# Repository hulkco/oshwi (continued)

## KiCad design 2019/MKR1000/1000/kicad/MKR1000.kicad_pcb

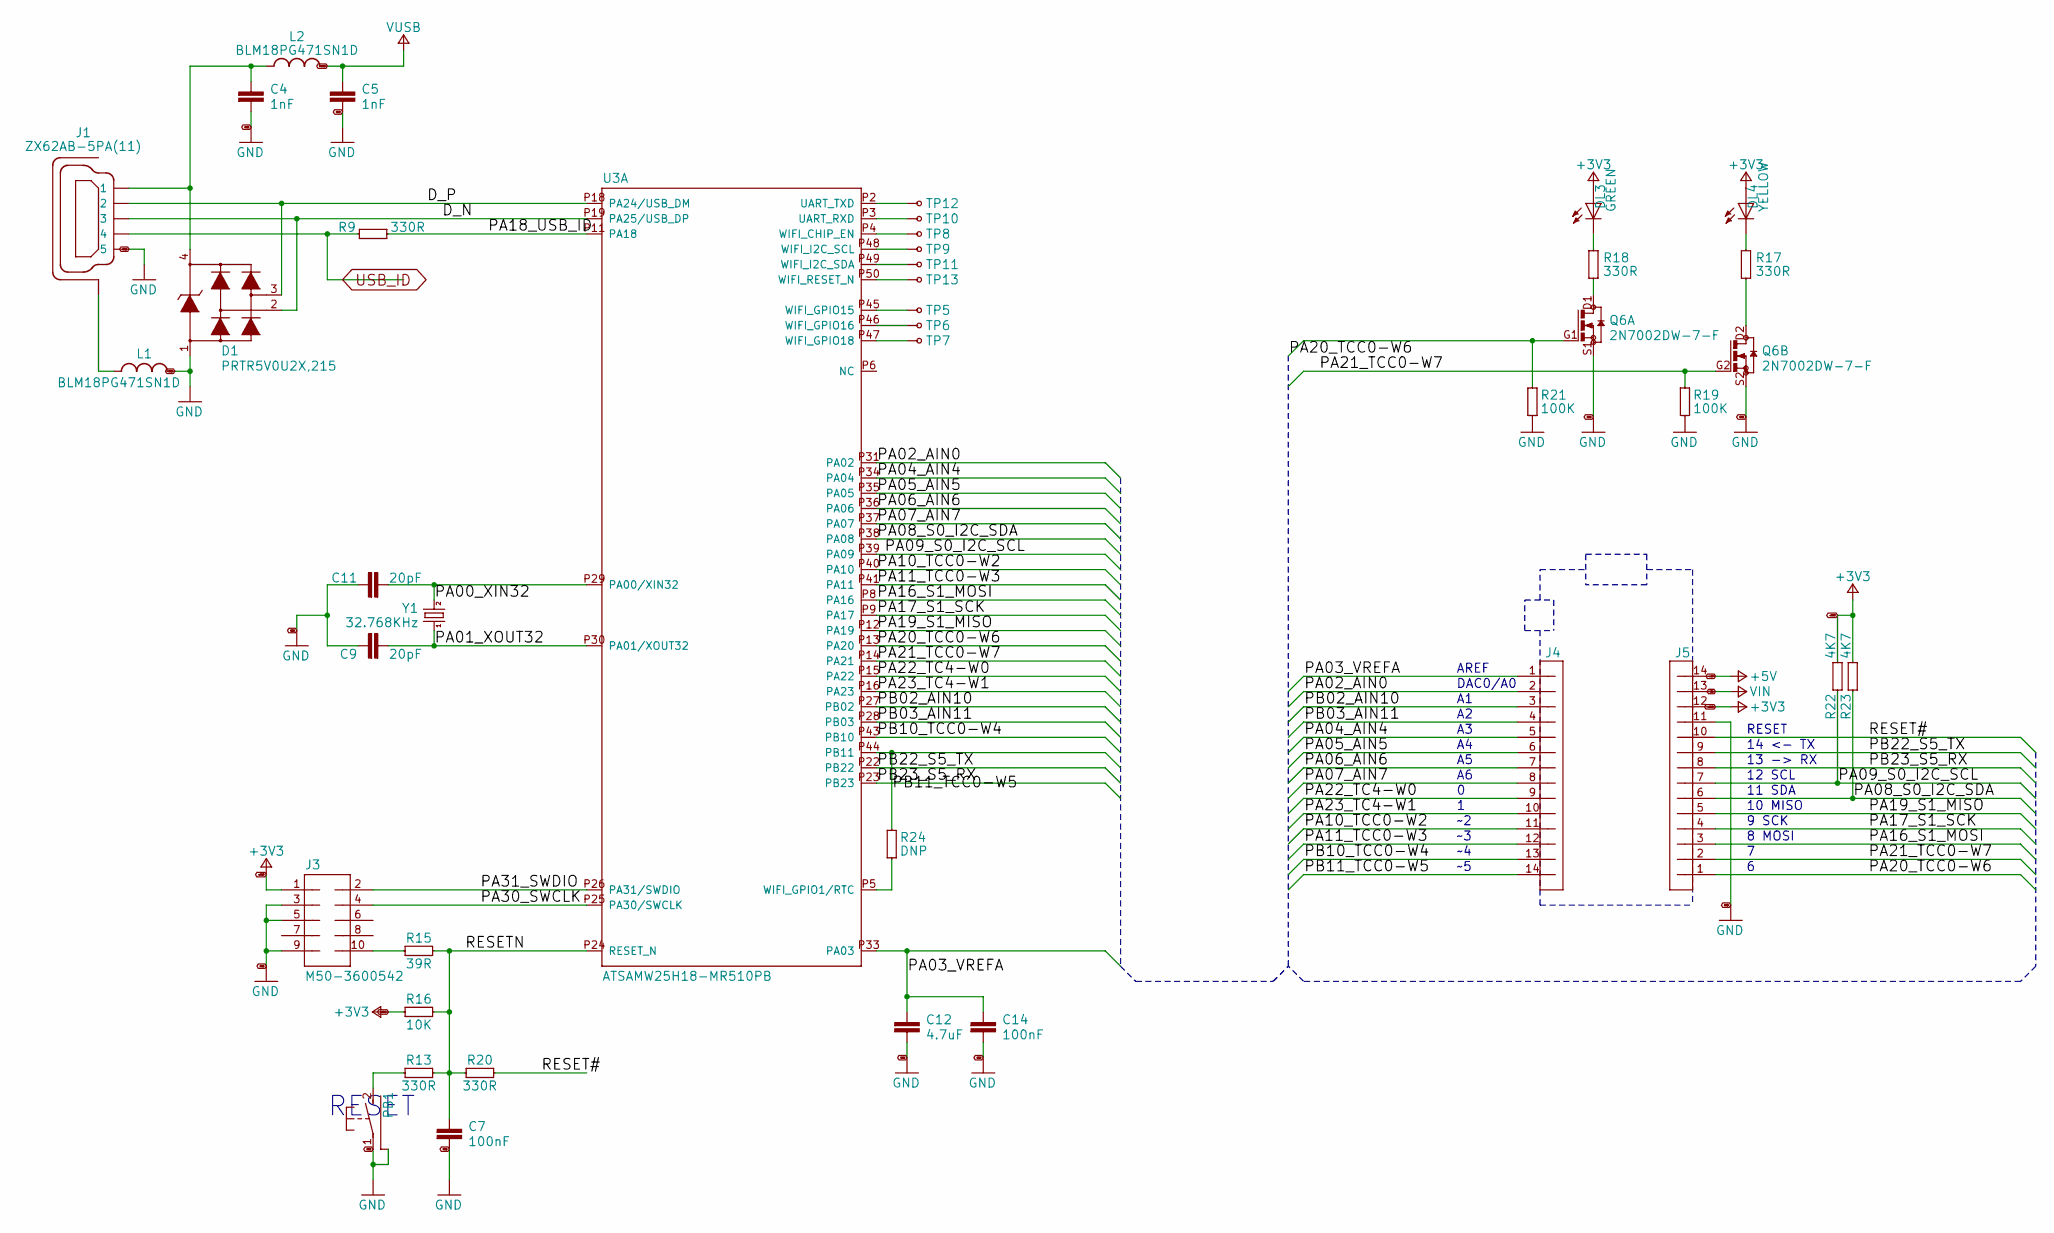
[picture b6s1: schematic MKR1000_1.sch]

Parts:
C4, C5: 1nF; 0402-1005X55N
C7, C14: 100nF; 0402-1005X55N
C9, C11: 20pF; 0402-1005X55N
C12: 4.7uF; 0402-1005X55N
D1: PRTR5V0U2X,215; SOT190P230X110-4N
DL3: GREEN; LEDC1608X80N-AK
DL4: YELLOW; LEDC1608X80N-AK
J1: ZX62AB-5PA(11); USBMICRO-ZX62-AB-5PA
J3: M50-3600542; FCI-MINITEK127HDR-10
J4, J5: DNP; STRIP-14-MODULI-A11
L1, L2: BLM18PG471SN1D; 0603-1608X90N
PB1: PTS820; PULS-45X29-PST820
Q6: 2N7002DW-7-F; SOT65P210X110-6AN-DM
R9, R13, R17, R18, R20: 330R; 0402-1005X55N
R15: 39R; 0402-1005X55N
R16: 10K; 0402-1005X55N
R19, R21: 100K; 0402-1005X55N
R22, R23: 4K7; 0402-1005X55N
R24: DNP; 0402-1005X55N
TP5, TP6, TP7, TP8, TP9, TP10, TP11, TP12, TP13: TESTPAD; PAD-SMD
U3: ATSAMW25H18-MR510PB; SAMW25
Y1: 32.768KHz; QUARZO-ABS07

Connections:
+3V3: DL3.A, DL4.A, J3.1, J5.12, R16.1, R22.2, R23.2; also elsewhere on the board
+5V: J5.14; also elsewhere on the board
/MKR1000_1/D_N: D1.2, J1.3, U3.P19 (PA25/USB_DP)
/MKR1000_1/D_P: D1.3, J1.2, U3.P18 (PA24/USB_DM)
/MKR1000_1/PA00_XIN32: C11.2, U3.P29 (PA00/XIN32), Y1.2
/MKR1000_1/PA01_XOUT32: C9.2, U3.P30 (PA01/XOUT32), Y1.1
/MKR1000_1/PA02_AIN0: J4.2, U3.P31 (PA02)
/MKR1000_1/PA03_VREFA: C12.1, C14.1, J4.1, U3.P33 (PA03)
/MKR1000_1/PA04_AIN4: J4.5, U3.P34 (PA04)
/MKR1000_1/PA05_AIN5: J4.6, U3.P35 (PA05)
/MKR1000_1/PA06_AIN6: J4.7, U3.P36 (PA06)
/MKR1000_1/PA07_AIN7: J4.8, U3.P37 (PA07)
/MKR1000_1/PA08_S0_I2C_SDA: J5.6, R23.1, U3.P38 (PA08)
/MKR1000_1/PA09_S0_I2C_SCL: J5.7, R22.1, U3.P39 (PA09)
/MKR1000_1/PA10_TCC0-W2: J4.11, U3.P40 (PA10)
/MKR1000_1/PA11_TCC0-W3: J4.12, U3.P41 (PA11)
/MKR1000_1/PA16_S1_MOSI: J5.3, U3.P8 (PA16)
/MKR1000_1/PA17_S1_SCK: J5.4, U3.P9 (PA17)
/MKR1000_1/PA18_USB_ID: R9.2, U3.P11 (PA18)
/MKR1000_1/PA19_S1_MISO: J5.5, U3.P12 (PA19)
/MKR1000_1/PA20_TCC0-W6: J5.1, Q6.G1 (G), R21.2, U3.P13 (PA20)
/MKR1000_1/PA21_TCC0-W7: J5.2, Q6.G2 (G), R19.2, U3.P14 (PA21)
/MKR1000_1/PA22_TC4-W0: J4.9, U3.P15 (PA22)
/MKR1000_1/PA23_TC4-W1: J4.10, U3.P16 (PA23)
/MKR1000_1/PA30_SWCLK: J3.4, U3.P25 (PA30/SWCLK)
/MKR1000_1/PA31_SWDIO: J3.2, U3.P26 (PA31/SWDIO)
/MKR1000_1/PB02_AIN10: J4.3, U3.P27 (PB02)
/MKR1000_1/PB03_AIN11: J4.4, U3.P28 (PB03)
/MKR1000_1/PB10_TCC0-W4: J4.13, U3.P43 (PB10)
/MKR1000_1/PB11_TCC0-W5: J4.14, R24.2, U3.P44 (PB11)
/MKR1000_1/PB22_S5_TX: J5.9, U3.P22 (PB22)
/MKR1000_1/PB23_S5_RX: J5.8, U3.P23 (PB23)
/MKR1000_1/RESET#: J5.10, R20.2
/MKR1000_1/RESETN: C7.1, R13.2, R15.2, R16.2, R20.1, U3.P24 (RESET_N)
GND: C4.2, C5.2, C7.2, C9.1, C11.1, C12.2, C14.2, D1.1, J1.5, J3.3, J3.5, J3.9, J5.11, L1.2, PB1.1, PB1.3 (SH), PB1.4 (SH), PB1.5 (SH), PB1.6 (SH), Q6.S1 (S), Q6.S2 (S), R19.1, R21.1; also elsewhere on the board
unnamed: C4.1, D1.4, J1.1, L2.1
unnamed: DL3.C, R18.2
unnamed: DL4.C, R17.2
unnamed: J1.6 (SH), J1.7 (SH), J1.8 (SH), J1.9 (SH), J1.10 (SH), J1.11 (SH), L1.1
unnamed: J3.10, R15.1
unnamed: PB1.2 (S), R13.1
unnamed: Q6.D1 (D), R18.1
unnamed: Q6.D2 (D), R17.1
unnamed: R24.1, U3.P5 (WIFI_GPIO1/RTC)
unnamed: TP5.1, U3.P45 (WIFI_GPIO15)
unnamed: TP6.1, U3.P46 (WIFI_GPIO16)
unnamed: TP7.1, U3.P47 (WIFI_GPIO18)
unnamed: TP8.1, U3.P4 (WIFI_CHIP_EN)
unnamed: TP9.1, U3.P48 (WIFI_I2C_SCL)
unnamed: TP10.1, U3.P3 (UART_RXD)
unnamed: TP11.1, U3.P49 (WIFI_I2C_SDA)
unnamed: TP12.1, U3.P2 (UART_TXD)
unnamed: TP13.1, U3.P50 (WIFI_RESET_N)
USB_ID: J1.4, R9.1; also elsewhere on the board
VIN: J5.13; also elsewhere on the board
VUSB: C5.1, L2.2; also elsewhere on the board

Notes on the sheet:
14 <- TX
13 -> RX
12 SCL
RESET
11 SDA
8 MOSI
9 SCK
10 MISO
AREF
DAC0/A0
~~2
~~3
~~4
~~5

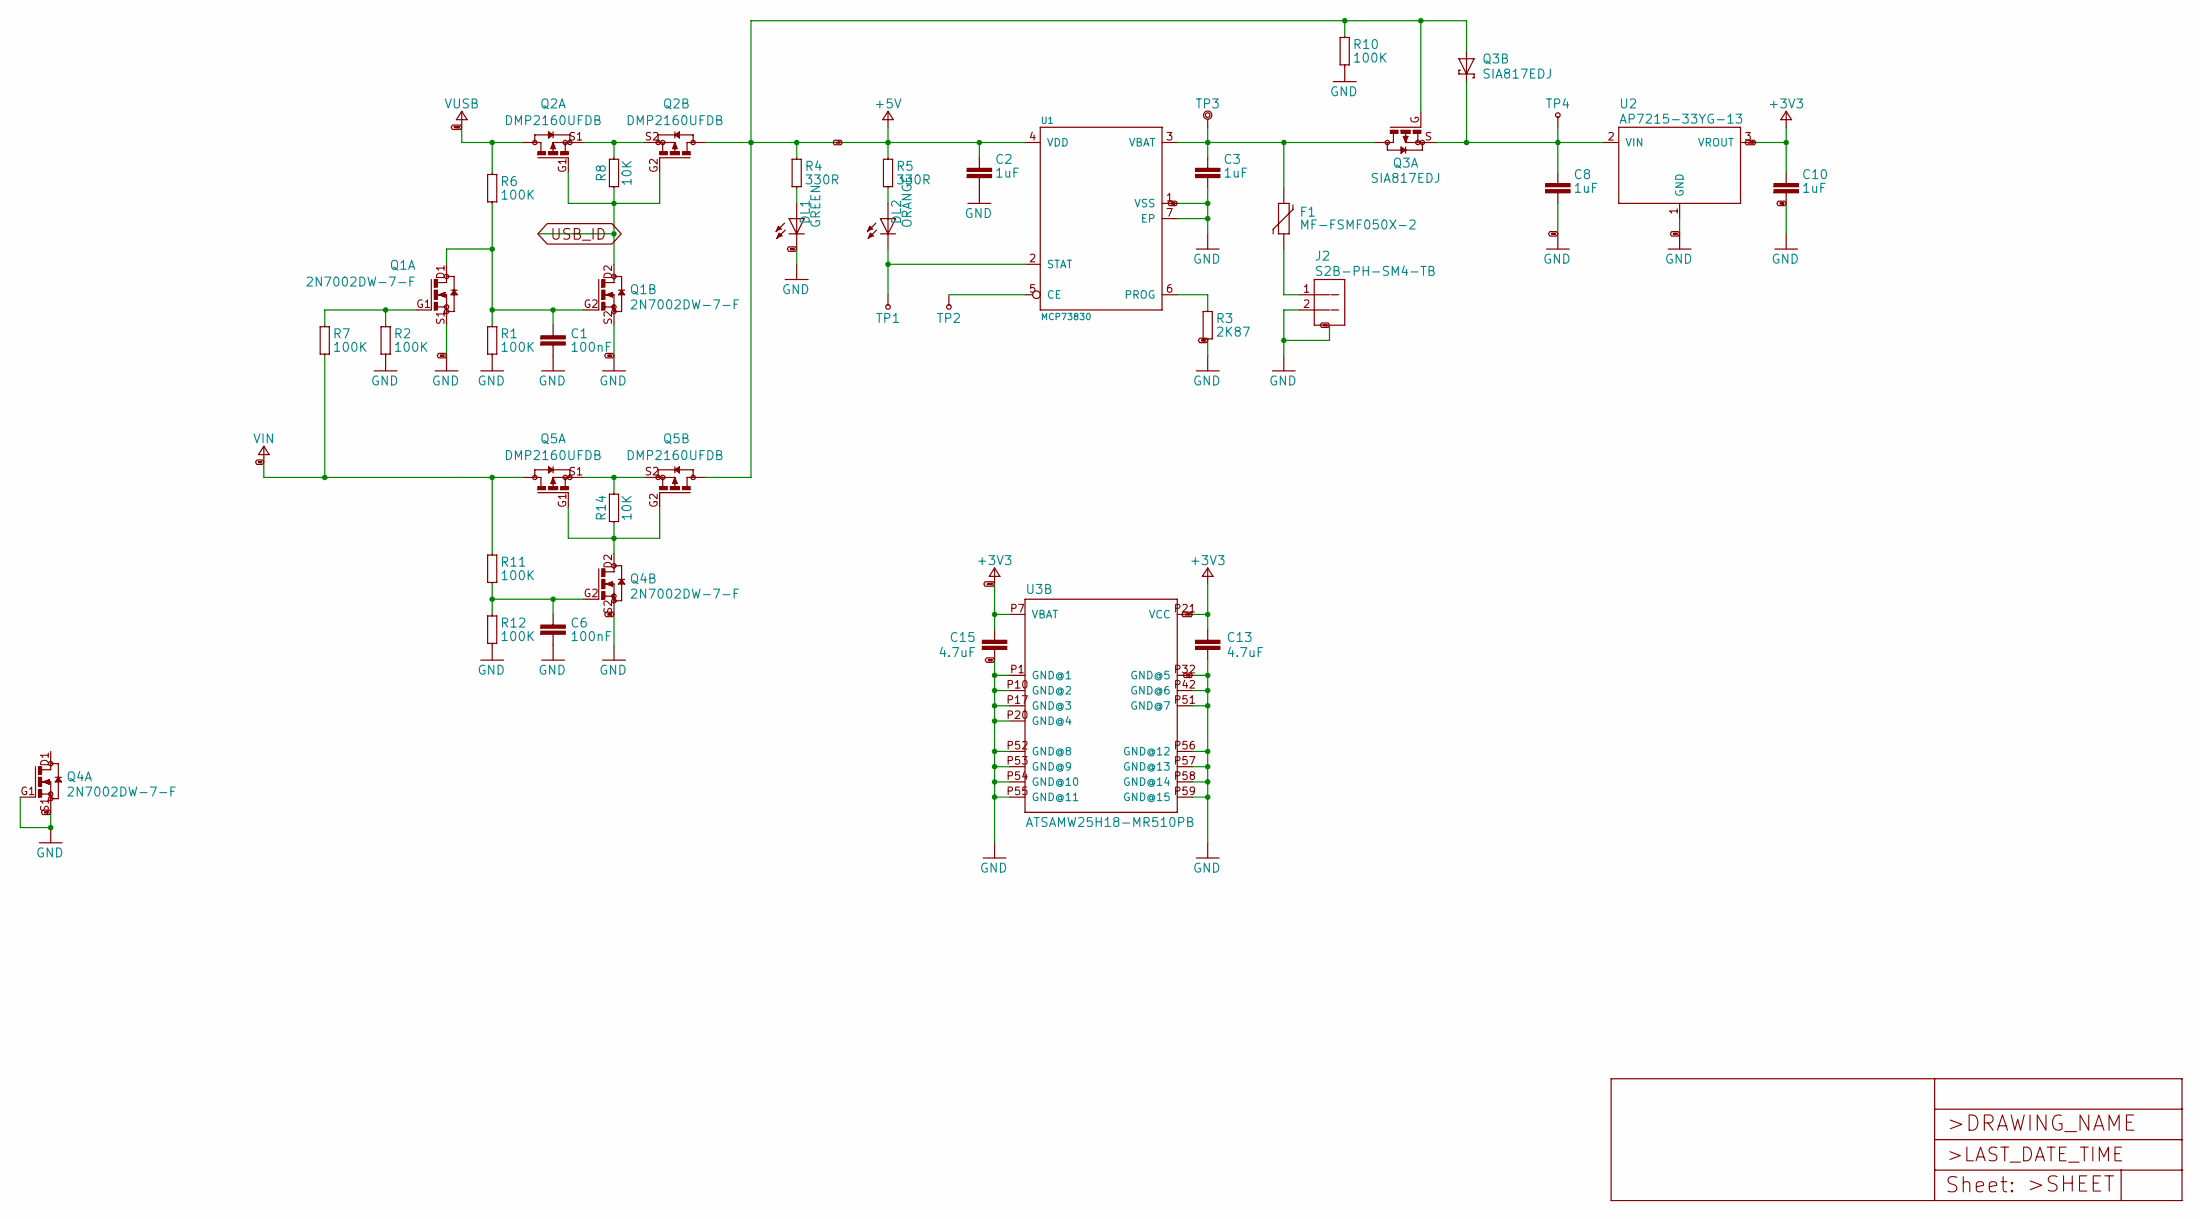
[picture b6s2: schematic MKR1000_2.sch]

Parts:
C1, C6: 100nF; 0402-1005X55N
C2, C3, C8, C10: 1uF; 0402-1005X55N; VOLTAGE 25V
C13, C15: 4.7uF; 0402-1005X55N
DL1: GREEN; LEDC1608X80N-AK
DL2: ORANGE; LEDC1608X80N-AK
F1: MF-FSMF050X-2; 0603-F1608X100N
FRAME2: Page 2; FRAME-NO-BAN-FRAMEONLY
J2: S2B-PH-SM4-TB; JST-S2B-PH-SM4-TB
Q1, Q4: 2N7002DW-7-F; SOT65P210X110-6AN-DM
Q2, Q5: DMP2160UFDB; SON65P200X200X60-8N-DM
Q3: SIA817EDJ; SON65P205X205X75-8N-MWSD
R1, R2, R6, R7, R10, R11, R12: 100K; 0402-1005X55N
R3: 2K87; 0805-R2013X50N
R4, R5: 330R; 0402-1005X55N
R8, R14: 10K; 0402-1005X55N
TP1, TP2, TP4: TESTPAD; PAD-SMD
TP3: TESTPOINT; TESTPOINT-60MLS-F0_9MM
U1: MCP73830; SON50P200X200X80-7N-EP160X60
U2: AP7215-33YG-13; SOT150P400X160-3N
U3: ATSAMW25H18-MR510PB; SAMW25

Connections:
+3V3: C10.1, C13.1, C15.1, U2.3 (VROUT), U3.P7 (VBAT), U3.P21 (VCC); also elsewhere on the board
+5V: C2.1, Q2.D2 (D), Q2.D2' (D), Q3.A, Q3.G, Q5.D2 (D), Q5.D2' (D), R4.2, R5.2, R10.2, U1.4 (VDD); also elsewhere on the board
GND: C1.2, C2.2, C3.2, C6.2, C8.2, C10.2, C13.2, C15.2, DL1.C, J2.2, J2.3 (SH), J2.4 (SH), Q1.S1 (S), Q1.S2 (S), Q4.G1 (G), Q4.S1 (S), Q4.S2 (S), R1.1, R2.1, R3.1, R10.1, R12.1, U1.1 (VSS), U1.7 (EP), U2.1 (GND), U3.P1 (GND@1), U3.P10 (GND@2), U3.P17 (GND@3), U3.P20 (GND@4), U3.P32 (GND@5), U3.P42 (GND@6), U3.P51 (GND@7), U3.P52 (GND@8), U3.P53 (GND@9), U3.P54 (GND@10), U3.P55 (GND@11), U3.P56 (GND@12), U3.P57 (GND@13), U3.P58 (GND@14), U3.P59 (GND@15); also elsewhere on the board
unnamed: C1.1, Q1.D1 (D), Q1.G2 (G), R1.2, R6.1
unnamed: C3.1, F1.2, Q3.D, Q3.D2 (D), TP3.1, U1.3 (VBAT)
unnamed: C6.1, Q4.G2 (G), R11.1, R12.2
unnamed: C8.1, Q3.K (C), Q3.K2 (C), Q3.S, TP4.1, U2.2 (VIN)
unnamed: DL1.A, R4.1
unnamed: DL2.A, R5.1
unnamed: DL2.C, TP1.1, U1.2 (STAT)
unnamed: F1.1, J2.1
unnamed: Q1.G1 (G), R2.2, R7.2
unnamed: Q2.S1 (S), Q2.S2 (S), R8.2
unnamed: Q4.D2 (D), Q5.G1 (G), Q5.G2 (G), R14.1
unnamed: Q5.S1 (S), Q5.S2 (S), R14.2
unnamed: R3.2, U1.6 (PROG)
unnamed: TP2.1, U1.5 (CE)
USB_ID: Q1.D2 (D), Q2.G1 (G), Q2.G2 (G), R8.1; also elsewhere on the board
VIN: Q5.D1 (D), Q5.D1' (D), R7.1, R11.2; also elsewhere on the board
VUSB: Q2.D1 (D), Q2.D1' (D), R6.2; also elsewhere on the board

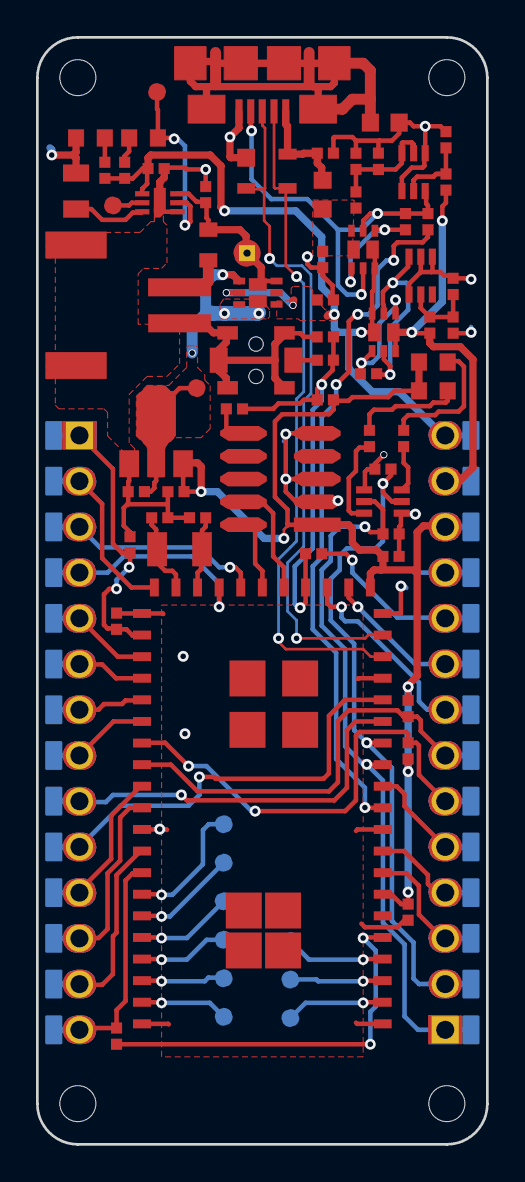
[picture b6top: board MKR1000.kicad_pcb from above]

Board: 2 copper layers, 25.0 x 61.5 mm, 82 parts (0 on the bottom side), 70 nets.

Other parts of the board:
@HOLE0, @HOLE1, @HOLE2, @HOLE3: (no value)
FRAME1: DNP; FRAME

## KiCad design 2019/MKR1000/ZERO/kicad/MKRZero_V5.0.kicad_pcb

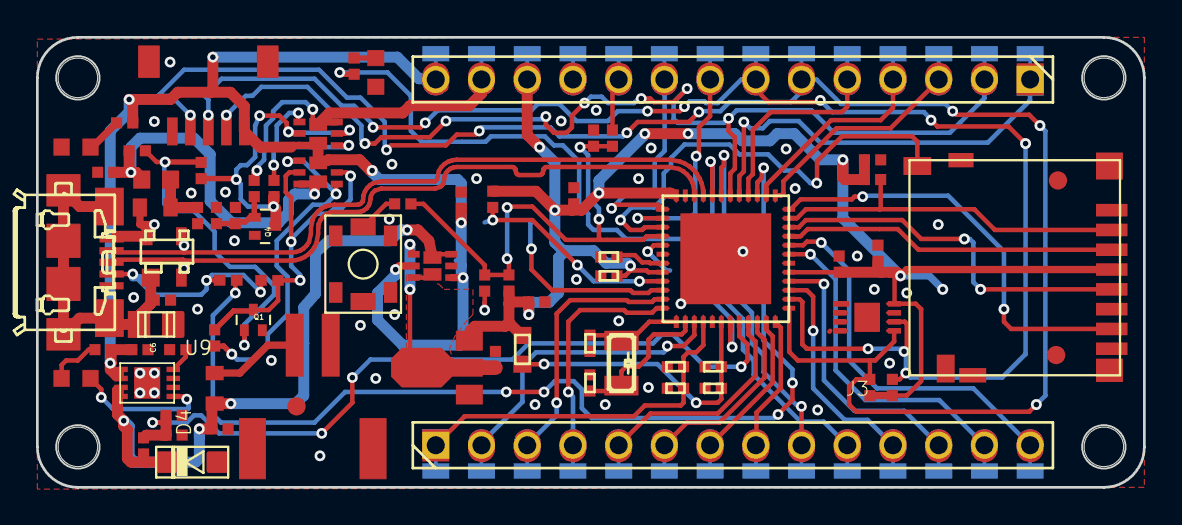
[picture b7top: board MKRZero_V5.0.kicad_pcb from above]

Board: 2 copper layers, 61.5 x 25.0 mm, 94 parts (0 on the bottom side), 67 nets.

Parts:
@HOLE0, @HOLE1, @HOLE2, @HOLE3: (no value)
BATT+1: PTR1B1,27; B1,27
BATT-1: PTR1B1,27; B1,27
C1, C7, C13, C14, C15, C19, C28, C29, C30, C33: 100nF; 0402-1005X55N
C2, C3, C8, C10, C32: 1uF; 0402-1005X55N
C4, C5: 1nF; 0402-1005X55N
C6: 4.7nF; C0805
C9, C11: 20pF; 0402-1005X55N
C12, C27: 4.7uF; 0402-1005X55N
D1: PRTR5V0U2X,215; SOT190P230X110-4N
D2, D3: PMEG2005EL; SODFL1008X40N-882D
D4: PMEG6020AELRX; SMA_DO123
D+1: PTR1B1,27; B1,27
D-1: PTR1B1,27; B1,27
DL1: GREEN; LEDC1608X80N-AK
DL2: ORANGE; LEDC1608X80N-AK
DL3: YELLOW; LEDC1608X80N-AK
ESCL1: PTR1B1,27; B1,27
ESDA1: PTR1B1,27; B1,27
EWK1: PTR1B1,27; B1,27
F1, F2: MF-FSMF050X-2; 0603-F1608X100N
FD1, FD2, FD3: FIDUCIALMOUNT; FIDUCIAL-MOUNT
J1: ZX62-AB-5PA(31); USBMICRO-ZX62-AB-5PA
J2: S2B-PH-SM4-TB; JST-S2B-PH-SM4-TB
J3: AMPHENOL_114-00841-68
J4, J5: DNP; STRIP-14-MODULI-A11
J7: SM05B-SRSS-TB
J8: 2X3_SMD_MALE; 2X3_SMT
L2, L6: BLM18PG471SN1D; 0603-1608X90N
PA28: TPB2,54; B2,54
Q1, Q4: 2N7002T; SOTFL50P160X78-3
Q2, Q5: DMP2160UFDB; SON65P200X200X60-8N-DM
Q3: SIA817EDJ; SON65P205X205X75-8N-MWSD
R1, R4, R5, R13, R18, R20: 330R; 0402-1005X55N
R2: 1M; 0402-1005X55N
R3: 2K87; 0402-1005X55N
R6, R10, R11, R12, R17: 100K; 0402-1005X55N
R7: 1K; 0402-1005X55N
R8, R14, R16: 10K; 0402-1005X55N
R9: 1M2; 0402-1005X55N
R15: 39R; 0402-1005X55N
R19: 330k; 0402-1005X55N
R22, R23: DNP; 0402-1005X55N
U2: AP7215-33YG-13; SOT150P400X160-3N
U3: ATSAMD21G18A-48; QFN50P700X700X90-49XN-EPSQ515
U4: ATECC508A-DNP; SON50P300X200X60-9N-EP160X140
U9: MCP738312X3DFN; 2X3DFN
U$5, U$6, U$7, U$8: MH_RND_F_2.2MM_NM
U$9: PUSHBUTTON2; C&K_PTS820_NOPEGS
USB_ID1: PTR1B1,27; B1,27
VUSB1: PTR1B1,27; B1,27
Y1: 32.768KHz; QUARZO-ABS07

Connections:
+3V3: C1.1, C10.1, C19.1, C28.1, C29.1, C33.1, J3.4, J5.12, J8.1, L6.1, R7.2, R16.2, R17.2, R22.2, R23.2, U2.3, U3.17, U3.36, U3.44, U4.8
+5V: C2.1, J5.14, J7.1, Q2.D2, Q2.D2', Q3.A, Q3.G, Q5.D2, Q5.D2', R4.2, R5.2, R10.2, U9.1, U9.2
/MKRZero_V5.0_1/PA00_XIN32: C11.2, U3.1, Y1.2
/MKRZero_V5.0_1/PA01_XOUT32: C9.2, U3.2, Y1.1
/MKRZero_V5.0_1/PA02_AIN0: J4.2, U3.3
/MKRZero_V5.0_1/PA03_VREFA: C12.1, C14.1, J4.1, U3.4
/MKRZero_V5.0_1/PA04_AIN4: J4.5, U3.9
/MKRZero_V5.0_1/PA05_AIN5: J4.6, U3.10
/MKRZero_V5.0_1/PA06_AIN6: J4.7, U3.11
/MKRZero_V5.0_1/PA07_AIN7: J4.8, U3.12
/MKRZero_V5.0_1/PA08_S0_I2C_SDA: ESDA1.PP, J5.6, J7.4, R23.1, U3.13, U4.5
/MKRZero_V5.0_1/PA09_S0_I2C_SCL: ESCL1.PP, J5.7, J7.3, R22.1, U3.14, U4.6
/MKRZero_V5.0_1/PA10_TCC0-W2: J4.11, U3.15
/MKRZero_V5.0_1/PA11_TCC0-W3: J4.12, U3.16
/MKRZero_V5.0_1/PA12_S2_MOSI: J3.3, U3.21
/MKRZero_V5.0_1/PA13_S2_SCK: J3.5, U3.22
/MKRZero_V5.0_1/PA14_S2_NSS: J3.2, R17.1, U3.23
/MKRZero_V5.0_1/PA15_S2_MISO: J3.7, U3.24
/MKRZero_V5.0_1/PA16_S1_MOSI: J5.3, U3.25
/MKRZero_V5.0_1/PA17_S1_SCK: J5.4, U3.26
/MKRZero_V5.0_1/PA18_USB_ID: D3.A, U3.27
/MKRZero_V5.0_1/PA19_S1_MISO: J5.5, U3.28
/MKRZero_V5.0_1/PA20_TCC0-W6: J5.1, U3.29
/MKRZero_V5.0_1/PA21_TCC0-W7: EWK1.PP, J5.2, J7.2, U3.30
/MKRZero_V5.0_1/PA22_TC4-W0: J4.9, U3.31
/MKRZero_V5.0_1/PA23_TC4-W1: J4.10, U3.32
/MKRZero_V5.0_1/PA27_CD: J3.CD1, U3.39
/MKRZero_V5.0_1/PA30_SWCLK: J8.4, R7.1, U3.45
/MKRZero_V5.0_1/PA31_SWDIO: J8.2, U3.46
/MKRZero_V5.0_1/PB02_AIN10: J4.3, U3.47
/MKRZero_V5.0_1/PB03_AIN11: J4.4, U3.48
/MKRZero_V5.0_1/PB08_LED: R18.1, U3.7
/MKRZero_V5.0_1/PB10_TCC0-W4: J4.13, U3.19
/MKRZero_V5.0_1/PB11_TCC0-W5: J4.14, U3.20
/MKRZero_V5.0_1/PB22_S5_TX: J5.9, U3.37
/MKRZero_V5.0_1/PB23_S5_RX: J5.8, U3.38
/MKRZero_V5.0_1/RESET#: J5.10, R20.2
/MKRZero_V5.0_1/RESETN: C7.1, R13.2, R15.2, R16.1, R20.1, U3.40
/MKRZero_V5.0_1/USB_N: D1.3, D-1.PP, J1.2, U3.33
/MKRZero_V5.0_1/USB_P: D1.2, D+1.PP, J1.3, U3.34
GND: BATT-1.PP, C1.2, C2.2, C3.2, C4.2, C5.2, C6.2, C7.2, C8.2, C9.1, C10.2, C11.1, C12.2, C13.2, C14.2, C15.2, C19.2, C27.2, C28.2, C29.2, C30.2, C32.2, C33.2, D4.A, DL1.C, DL3.C, J1.5, J2.2, J2.3, J2.4, J3.6, J3.CD2, J3.SH1, J3.SH2, J3.SH3, J3.SH4, J5.11, J7.5, J7.SH1, J7.SH2, J8.5, Q1.S, Q4.S, R2.1, R3.1, R9.1, R10.1, R12.1, U2.1, U3.5, U3.18, U3.35, U3.42, U3.49, U4.4, U9.6, U9.PAD, U$9.1, U$9.2, U$9.3, U$9.4, U$9.5
unnamed: C4.1, F2.1, L2.1
unnamed: C6.1, D1.1, J1.6, J1.7, J1.8, J1.9, J1.10, J1.11, R2.2
unnamed: C8.1, Q3.K, Q3.K2, Q3.S, U2.2
unnamed: C13.1, R9.2, R19.1, U3.8
unnamed: C15.1, Q4.G, R11.1, R12.2
unnamed: C27.1, C30.1, L6.2, U3.6
unnamed: C32.1, U3.43
unnamed: D1.4, F2.2, J1.1, VUSB1.PP
unnamed: D2.A, Q1.D, Q2.G1, Q2.G2, R8.1
unnamed: DL1.A, R4.1
unnamed: DL2.A, R5.1
unnamed: DL2.C, U9.5
unnamed: DL3.A, R18.2
unnamed: F1.1, J2.1
unnamed: J8.3, R15.1
unnamed: PA28.PP, U3.41
unnamed: Q1.G, R1.2, R6.1
unnamed: Q2.S1, Q2.S2, R8.2
unnamed: Q4.D, Q5.G1, Q5.G2, R1.1, R14.1
unnamed: Q5.S1, Q5.S2, R14.2
unnamed: R3.2, U9.8
unnamed: R13.1, U$9.6
USB_ID: D2.C, D3.C, J1.4, USB_ID1.PP
VBATT: BATT+1.PP, C3.1, D4.C, F1.2, Q3.D, Q3.D2, R19.2, U9.3, U9.4
VIN: J5.13, Q5.D1, Q5.D1', R11.2
VUSB: C5.1, L2.2, Q2.D1, Q2.D1', R6.2

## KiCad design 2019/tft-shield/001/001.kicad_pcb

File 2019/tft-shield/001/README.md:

# TFT Shield 0.96 Screen

## Warnings
Under develoment!!!

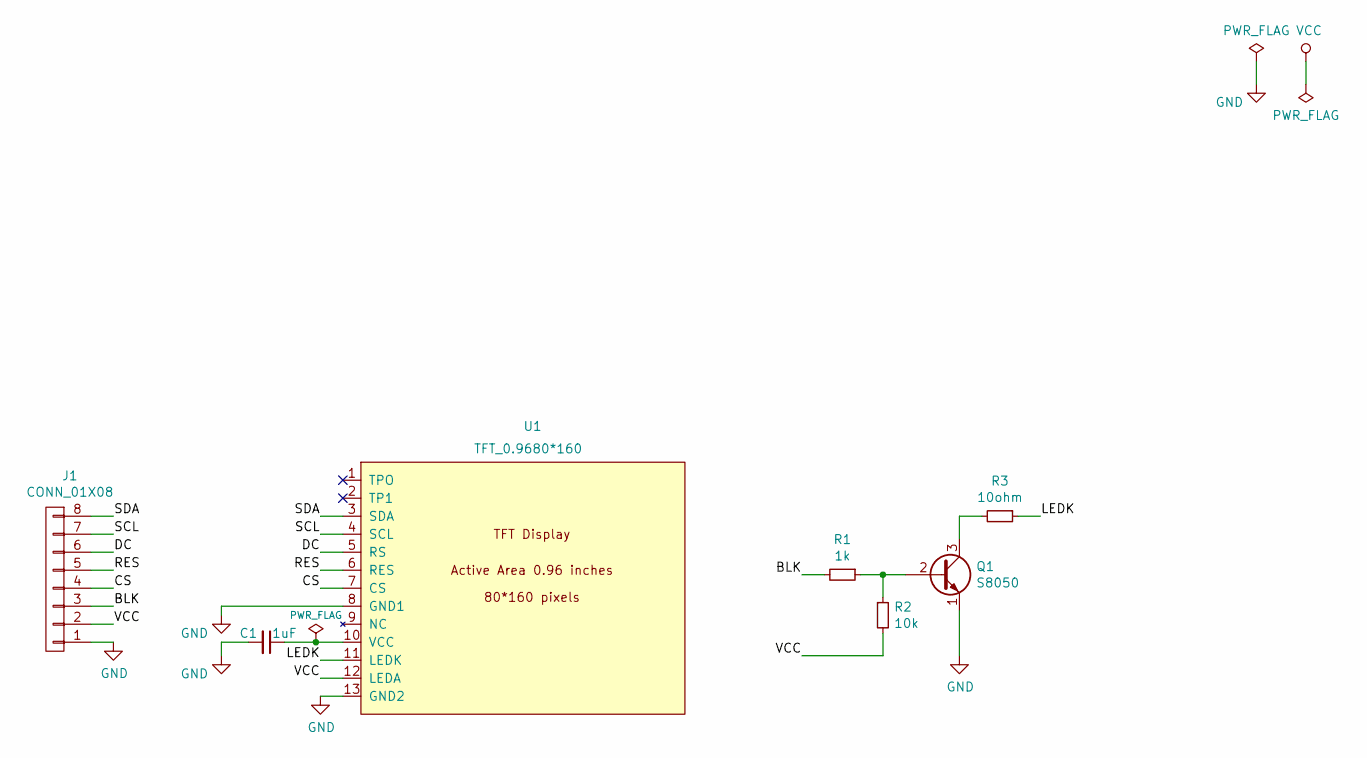
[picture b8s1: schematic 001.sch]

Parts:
C1: 1uF; C_0805_2012Metric_Pad1.15x1.40mm_HandSolder
J1: CONN_01X08; PinSocket_1x08_P2.54mm_Vertical
Q1: S8050; SOT-23
R1: 1k; R_0805_2012Metric_Pad1.15x1.40mm_HandSolder
R2: 10k; R_0805_2012Metric_Pad1.15x1.40mm_HandSolder
R3: 10ohm; R_0805_2012Metric_Pad1.15x1.40mm_HandSolder
U1: TFT_0.9680*160; TFT_0.96_SPI

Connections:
/BLK: J1.3, R1.2
/CS: J1.4, U1.7 (CS)
/DC: J1.6, U1.5 (RS)
/LEDK: R3.1, U1.11 (LEDK)
/RES: J1.5, U1.6 (RES)
/SCL: J1.7, U1.4 (SCL)
/SDA: J1.8, U1.3 (SDA)
GND: C1.2, J1.1, Q1.1 (E), U1.8 (GND1), U1.13 (GND2)
unnamed: C1.1, U1.10 (VCC)
unnamed: Q1.2 (B), R1.1, R2.1
unnamed: Q1.3 (C), R3.2
VCC: J1.2, R2.2, U1.12 (LEDA)

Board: 2 copper layers, 7 parts (6 on the bottom side), 12 nets, no tracks yet.

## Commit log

2017-07-16 :neckbeard: Added .gitattributes & .gitignore files
2017-07-16 Upload
    Just firts upload, remember this a very alpha release
2017-08-01 Some changes
    Add, pull up resistor, capacitors for filtering and routing.
2017-08-12 Final release OSHWDem Badge with PCBWay sponsorship
2017-08-12 Final Release of OSHWDem Badge 2017
    Final Release of OSHWDem Badge with PCBWay sponsorship
2017-08-12 add Libraries
2017-08-12 move to Libraries
2017-08-12 Change Label D2
2017-08-12 update images
2017-08-23 Set theme jekyll-theme-cayman
2017-09-01 Folders version
2017-09-01 Some minors canges
2017-09-01 Some files
2017-09-01 Some changes
2017-09-01 Test
2017-09-01 Upload OshPark Version
2017-09-01 Upload PCBWay Version
2017-09-23 Auto stash before merge of "master" and "origin/master"
2017-09-23 Rev 1
2017-10-15 Changes an add Mazportal version
2018-02-20 Add Schematic PDF
2018-03-04 Add Fritzing Parts
2018-03-19 Update Buttom Reset description
2019-04-27 Move to a year directory
2019-04-27 Update footprints
2019-04-27 Update directory release 2017
2019-04-27 Upload ArtWork to release 2017
2019-04-29 Update schematic
2019-04-29 Update directory tft name
2019-04-29 Add Schematic for TFT & PyPortal
2019-04-29 Minors updates
2019-05-03 More examples TFTs
2019-05-07 Add Flash Breakout
2019-05-13 Minor updates
2019-05-20 Update Nano
2019-05-20 Add Info TFT
2019-05-22 Remove Bad commits & Update SPI Symbol
2019-05-22 Update SAMD21G Symbol & add CE schematic
2019-05-22 Add CE Symbol
2019-05-23 Update Schematic SAMD21G & SPI
2019-05-23 Add tft-shield project
2019-05-24 Add Draw settings in Docs TFT
2019-05-27 Change Directory structure
2019-05-28 Add OshwiM0 resumen
2019-05-28 Update Symbol MicroUSB
2019-06-11 Add Changes to Oshwi 2019 Badge
2019-06-14 Add changes tft_shield
2019-06-15 Add some changess & 3d model
2019-06-15 Update 3d Model
2019-06-16 Create TFT Library
2019-06-16 Various updates
2019-06-18 Add Arduino Code for Generic TFT 0.96
2019-06-26 Add SPI Bus Doctos
2019-06-27 Changes MicroSD
2019-06-27 Add ESP32 pinout
2019-06-27 Move TFT pinout because Micro SD problem
2019-06-28 Add Bast SERCOM PinOut
2019-07-08 Add new Docs to Library
2019-07-08 Minor changes Micro SD pinout
2019-07-09 Update ArtWork Oshwi
2019-07-10 Add ESP32 Pico Docs
2019-07-11 Add OshwiESP32 2019
2019-07-12 Add WS2812B-2020 footprint
2019-07-14 Add changes to ArtWork 2019
2019-07-18 Continue the Design of ESP32 Badge
2019-07-22 update es8266 design
